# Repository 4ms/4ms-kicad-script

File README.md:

# 4ms Kicad Scripts
***All of these scripts are Works In Progress. Use at your own risk!!***

## Scripts

  * `makefp`: PCB plugins (python scripts) to create a Eurorack faceplate from a PCB. Automatically determines smallest standard size that will fit, creates an outline and rail mounting slots, replaces all panel components with holes (using a look-up table that you must edit if you're not using standard 4ms libraries), removes all SMT components and traces, and creates a copper GND plane on the back (connecting all holes to it). It's not perfect and often requires some manual clean-up.

  * `BOM-scripts`: EEschema plugins that produce a BOM properly formatted for a PCBA service.

  * `resistor_generator`: Generate a Kicad symbol library of standard resistor values (E96+E24) for a given SMT package and tolerance. Searches JLCPCB's database to populate a JLCPCB part number field, and also generates a valid Yageo part number.

  * `lib_scripts`: a series of scripts used to create a KiCad symbol library from a BOM CSV file and a group of schematics that share common parts. Originally written for the [OpenVentilator](https://gitlab.com/openventilator/openventilator) project. When importing projects into Kicad from other EDA software, a library is created for each imported project, so these scripts are handy for essentially merging all the individual project libraries into a single shared library (and throw in some useful information from a BOM file while it's at it). We also have used these scripts to create the latest 4ms symbol libraries (atomic part library) since we have all MPN etc information in the BOM files.

  * `lib_scripts/symLibConversion`: This script does some of the rote search-and-replacement when updating a legacy 4ms library schematic to the new atomic libraries.

  * `net_tools`: Some PCBnew python plugins for assigning nets to large amounts of items.

  * `grep-replace-globallabel-with-locallabel`: regex to replace all global labels with local labels in eechema. 

  * `XY-pos-file-convert`: A simple python script to convert Kicad's XY position file format to the one JLCPCB expects.

#### Deprecated Utilities ####

  * picknplace_assistant: Creates PDF files of front and back of PCB, showing the placement of each component. No longer being supported, as we've switched to using [Interactive HTML Bom](https://github.com/openscopeproject/InteractiveHtmlBom).

  * update\_kicad: OSX only. After you download and mount a Kicad nightly DMG, run this script to handle installing all the files, and properly merging the global fp/sym\_lib\_table files without having to manually add the 4ms libraries. This script also preserves your packages3d folder. No longer being supported, as our new library technique doesn't require modifying global library tables.

  * `gerbv shortcuts`. These are meant to be used with the old legacy gEDA gerbv program (not kicad's gerbv). They are templates that set the layer order and coloring to a standard format.

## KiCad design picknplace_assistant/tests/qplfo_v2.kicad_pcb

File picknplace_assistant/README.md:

Creates PDF files showing the placement of every component.

Forked from https://gist.github.com/pwuertz/152f15b2dadca9a74039aeab944714af

The pnpassist.py script can be run on the command line or in the PCB python terminal. The files in the plugin folders can be installed as plugins (see "How to install a plugin.md" file one directory up)

__Todo: Fork this in github/gist instead of just copying and modifying__

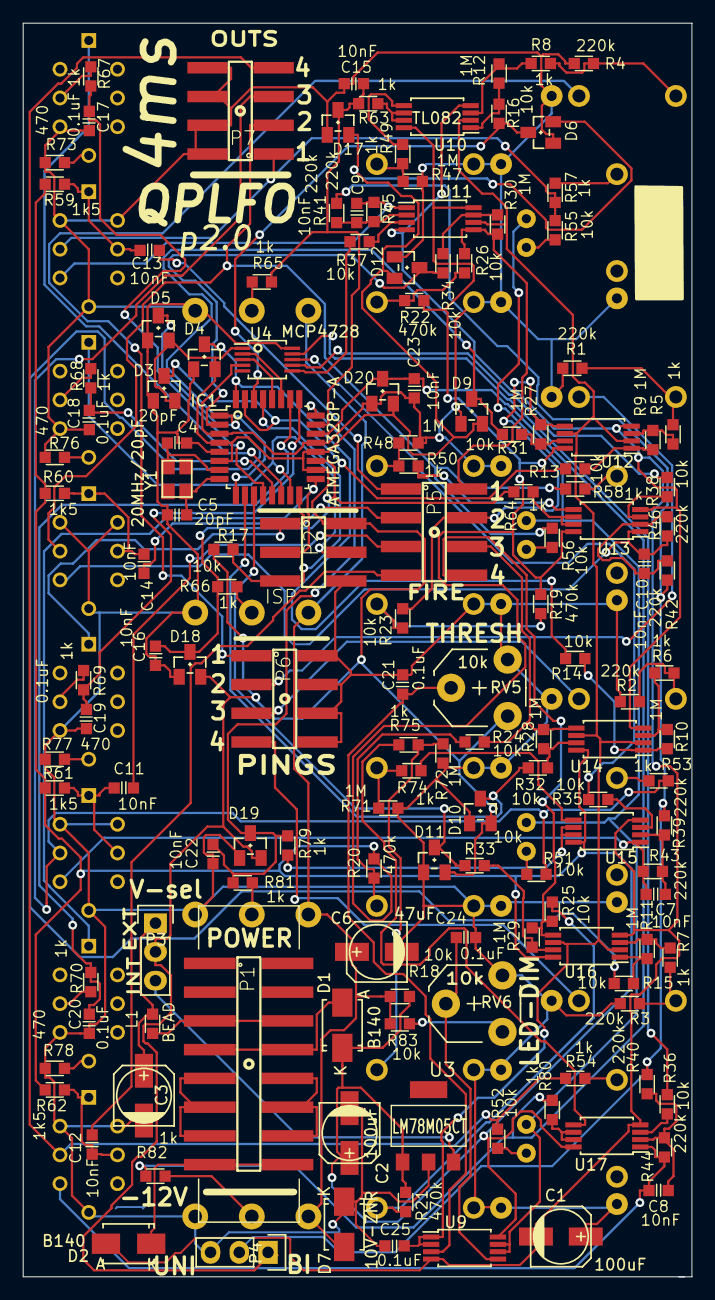
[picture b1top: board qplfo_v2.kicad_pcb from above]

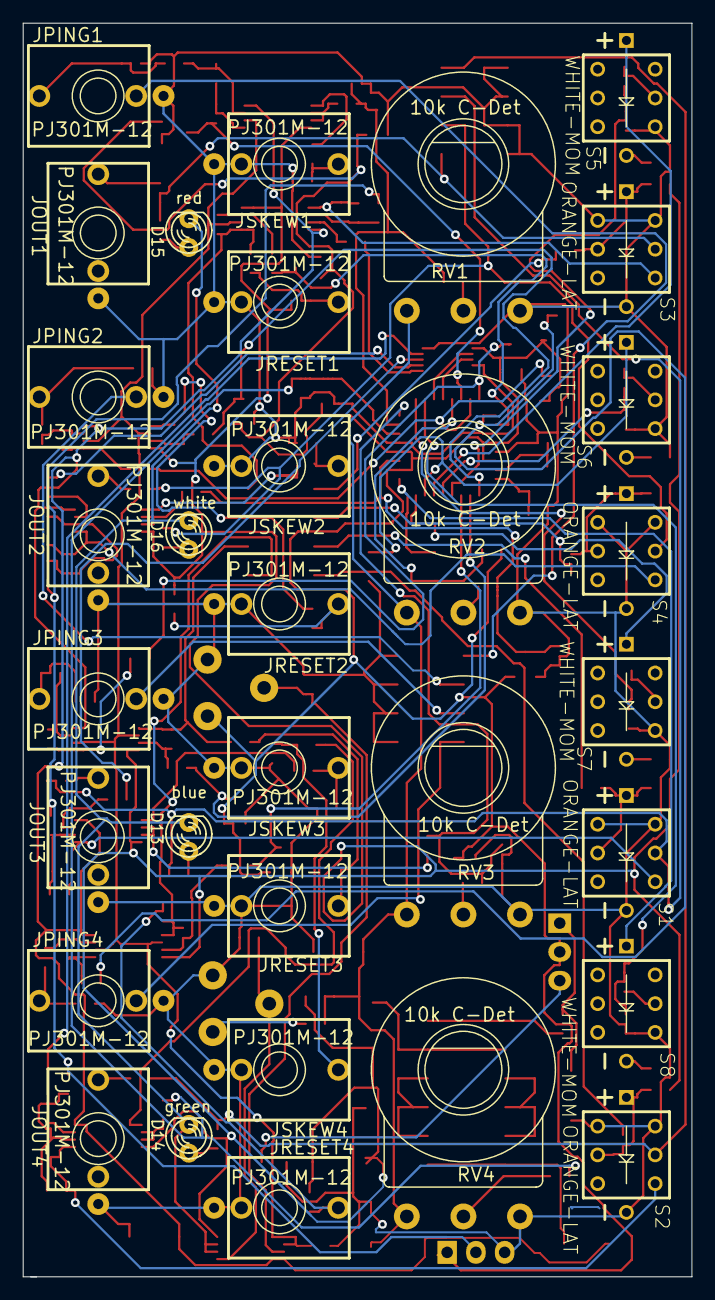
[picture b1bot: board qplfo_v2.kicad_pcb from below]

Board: 2 copper layers, 59.1 x 110.7 mm, 178 parts (32 on the bottom side), 131 nets.

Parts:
C1, C2, C3: 100uF; c_elec_5x5.3
C4, C5: 20pF; C0603
C6: 47uF; c_elec_5x5.3
C7, C8, C9, C10, C11, C12, C13, C14, C15, C16, C22, C23: 10nF; C0603
C17, C18, C19, C20, C21, C24, C25: 0.1uF; C0603
D1, D2: B140; Diode-SMA_Standard
D3, D4, D5, D6, D9, D10, D11, D12, D17, D18, D19, D20: BAT54S; SOT23
D7: 10V-ZNR; Diode-SMA_Standard
D13: blue; LED-3MM
D14: green; LED-3MM
D15: red; LED-3MM
D16: white; LED-3MM
IC1: ATMEGA328P-A; TQFP-32_7x7mm_Pitch0.8mm
JOUT1, JOUT2, JOUT3, JOUT4: PJ301M-12; PJ301M-12-FIX
JPING1, JPING2, JPING3, JPING4: PJ301M-12; PJ301M-12-FIX
JRESET1, JRESET2, JRESET3, JRESET4: PJ301M-12; PJ301M-12-FIX
JSKEW1, JSKEW2, JSKEW3, JSKEW4: PJ301M-12; PJ301M-12-FIX
L1: BEAD; R0603
P1: HE10-16; HEADER-2X8-SMT-SHROUDED
P2: ISP; HEADER-2X3-SMT
P3, P4: HEADER-MALE-1X3-TH; Pin_Header_Straight_1x03
P5: FIRE; HEADER-2X4-SMT
P6: PINGS; HEADER-2X4-SMT
P7: OUTS; HEADER-2X4-SMT
R1, R2, R3, R4, R39, R40, R41, R42, R43, R44, R45, R46: 220k; R0603
R5, R6, R7, R8, R49, R50, R53, R54, R57, R58, R63, R64, R65, R66, R67, R68, R69, R70, R74, R75, R79, R80, R81, R82: 1k; R0603
R9, R10, R11, R12, R27, R28, R29, R30, R47, R48, R71, R72: 1M; R0603
R13, R14, R15, R16, R17, R18, R23, R24, R25, R26, R31, R32, R33, R34, R35, R36, R37, R38, R51, R52, R55, R56, R83: 10k; R0603
R19, R20, R21, R22: 470k; R0603
R59, R60, R61, R62: 1k5; R0603
R73, R76, R77, R78: 470; R0603
RV1, RV2, RV3, RV4: 10k C-Det; 16MM-RV16AF-4A
RV5, RV6: 10k; Potentiometer_VishaySpectrol-Econtrim-Type36M
S1, S2, S3, S4: ORANGE-LAT; BUTTON-LED-PB61303
S5, S6, S7, S8: WHITE-MOM; BUTTON-LED-PB61303
U3: LM78M05CT; SOT223
U4: MCP4728; MSOP-10_3x3mm_Pitch0.5mm
U9, U10, U11, U12, U13, U14, U15, U16, U17: TL082; TSSOP-8_4.4x3mm_Pitch0.65mm
Y1: 20MHz/20pF; crystal_FA238-TSX3225

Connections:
+5V: D3.2, D4.2, D5.2, D6.2, D9.2, D10.2, D11.2, D12.2, D17.2, D18.2, D19.2, D20.2, IC1.4, IC1.6, IC1.18, IC1.20, P2.2, P3.2, P4.1, R17.1, RV5.1, U4.1
+12V: C2.1, D1.1, R18.2, R19.2, R20.2, R21.2, R22.2, R59.1, R60.1, R61.1, R62.1, U3.1, U9.8, U10.8, U11.8, U12.8, U13.8, U14.8, U15.8, U16.8, U17.8
-12V: C1.2, D2.2, U9.4, U10.4, U11.4, U12.4, U13.4, U14.4, U15.4, U16.4, U17.4
ENVRAW1: R37.2, U4.6
ENVRAW2: R38.2, U4.7
ENVRAW3: R35.2, U4.8
ENVRAW4: R36.2, U4.9
GND: C1.1, C2.2, C3.2, C4.2, C5.2, C6.2, C15.2, C16.2, C17.1, C18.1, C19.1, C20.1, C21.2, C22.2, C23.2, C24.2, C25.2, D3.1, D4.1, D5.1, D6.1, D7.1, D9.1, D10.1, D11.1, D12.1, D17.1, D18.1, D19.1, D20.1, IC1.3, IC1.5, IC1.21, JOUT1.2, JOUT2.2, JOUT3.2, JOUT4.2, JPING1.2, JPING2.2, JPING3.2, JPING4.2, JRESET1.2, JRESET1.3, JRESET2.2, JRESET2.3, JRESET3.2, JRESET3.3, JRESET4.2, JRESET4.3, JSKEW1.2, JSKEW1.3, JSKEW2.2, JSKEW2.3, JSKEW3.2, JSKEW3.3, JSKEW4.2, JSKEW4.3, P2.6, P4.3, P6.2, P6.4, P6.6, P6.8, P7.2, P7.4, P7.6, P7.8, R1.2, R2.2, R3.2, R4.2, R47.1, R48.1, R71.1, R72.1, R73.1, R76.1, R77.1, R78.1, RV1.3, RV2.3, RV3.3, RV4.3, RV5.3, RV6.3, S1.1, S1.4, S1.8, S2.1, S2.4, S2.8, S3.1, S3.4, S3.8, S4.1, S4.4, S4.8, S5.6, S6.6, S7.6, S8.6, U3.2, U4.4, U4.10
unnamed: C3.1, L1.2, P3.1
unnamed: C4.1, IC1.7, Y1.2
unnamed: C5.1, IC1.8, Y1.1
unnamed: C7.1, R43.1, S1.6, U15.1
unnamed: C7.2, R39.1, R43.2, U15.2
unnamed: C8.1, R44.1, S2.6, U17.1
unnamed: C8.2, R40.1, R44.2, U17.2
unnamed: C9.1, R45.1, S3.6, U11.1
unnamed: C9.2, R41.1, R45.2, U11.2
unnamed: C10.1, R46.1, S4.6, U13.1
unnamed: C10.2, R42.1, R46.2, U13.2
unnamed: C11.1, R61.2, S1.2, S1.7
unnamed: C12.1, R62.2, S2.2, S2.7
unnamed: C13.1, R59.2, S3.2, S3.7
unnamed: C14.1, R60.2, S4.2, S4.7
unnamed: C21.1, RV5.2, U9.3
unnamed: C24.1, RV6.2, U9.5
unnamed: D1.2, P1.7, P1.8
unnamed: D2.1, P1.15, P1.16
unnamed: D13.1, R51.1
unnamed: D14.1, R52.1
unnamed: D15.1, R55.1
unnamed: D16.1, R56.1
unnamed: IC1.27, U4.2
unnamed: IC1.28, U4.3
unnamed: IC1.29, P2.5, R17.2
unnamed: JOUT1.1, R57.1
unnamed: JOUT2.1, R58.1
unnamed: JOUT3.1, R53.1
unnamed: JOUT4.1, R54.1
unnamed: JPING1.1, R4.1, R8.2
unnamed: JPING2.1, R1.1, R5.2
unnamed: JPING3.1, R2.1, R6.2
unnamed: JPING4.1, R3.1, R7.2
unnamed: JRESET1.1, R22.1, R26.2
unnamed: JRESET2.1, R19.1, R23.2
unnamed: JRESET3.1, R20.1, R24.2
unnamed: JRESET4.1, R21.1, R25.2
unnamed: JSKEW1.1, R47.2, R49.2
unnamed: JSKEW2.1, R48.2, R50.2
unnamed: JSKEW3.1, R71.2, R74.2
unnamed: JSKEW4.1, R72.2, R75.2
unnamed: L1.1, P1.5, P1.6
unnamed: P1.10, P1.12, P1.14
unnamed: P1.9, P1.11, P1.13
unnamed: P3.3, U3.3
unnamed: R5.1, R9.2, U12.3
unnamed: R10.1, R14.1, U14.1
unnamed: R6.1, R10.2, U14.3
unnamed: R11.1, R15.1, U16.1
unnamed: R7.1, R11.2, U16.3
unnamed: R12.1, R16.1, U10.1
unnamed: R8.1, R12.2, U10.3
unnamed: R9.1, R13.1, U12.1
unnamed: R27.1, R31.1, U12.7
unnamed: R28.1, R32.1, U14.7
unnamed: R29.1, R33.1, U16.7
unnamed: R30.1, R34.1, U11.7
unnamed: R35.1, U15.3
unnamed: R36.1, U17.3
unnamed: R37.1, U11.3
unnamed: R38.1, U13.3
unnamed: R49.1, U10.5
unnamed: R50.1, U13.5
unnamed: R63.2, U10.6, U10.7
unnamed: R64.2, U13.6, U13.7
unnamed: R65.2, RV1.2
unnamed: R66.2, RV2.2
unnamed: R67.2, S5.5
unnamed: R68.2, S6.5
unnamed: R69.2, S7.5
unnamed: R70.2, S8.5
unnamed: R73.2, S5.8
unnamed: R74.1, U15.5
unnamed: R75.1, U17.5
unnamed: R76.2, S6.8
unnamed: R77.2, S7.8
unnamed: R78.2, S8.8
unnamed: R79.2, U15.6, U15.7
unnamed: R80.2, U17.6, U17.7
unnamed: R81.2, RV3.2
unnamed: R82.2, RV4.2
unnamed: R83.1, RV6.1
OUT1J: P7.1, R55.2, R57.2, S3.5
OUT2J: P7.3, R56.2, R58.2, S4.5
OUT3J: P7.5, R51.2, R53.2, S1.5
OUT4J: P7.7, R52.2, R54.2, S2.5
PING1: D6.3, IC1.30, R16.2
PING1SW: JPING1.3, P6.1
PING2: D3.3, IC1.31, R13.2
PING2SW: JPING2.3, P6.3
PING3: D4.3, IC1.32, R14.2
PING3SW: JPING3.3, P6.5
PING4: D5.3, IC1.1, R15.2
PING4SW: JPING4.3, P6.7
RESET1: D12.3, IC1.2, R34.2
RESET2: D9.3, IC1.9, R31.2
RESET3: D10.3, IC1.10, R32.2
RESET4: D11.3, IC1.11, R33.2
RESETMUTE1: C13.2, P5.1
RESETMUTE1B: P5.2, R26.1, R30.2, U11.5
RESETMUTE2: C14.2, P5.3
RESETMUTE2B: P5.4, R23.1, R27.2, U12.5
RESETMUTE3: C11.2, P5.5
RESETMUTE3B: P5.6, R24.1, R28.2, U14.5
RESETMUTE4: C12.2, P5.7
RESETMUTE4B: P5.8, R25.1, R29.2, U16.5
SKEW1-ADC: C15.1, D17.3, IC1.23, R63.1, R65.1
SKEW2-ADC: C22.1, D19.3, IC1.24, R79.1, R81.1
SKEW3-ADC: C16.1, D18.3, IC1.19, R64.1, R66.1
SKEW4-ADC: C23.1, D20.3, IC1.22, R80.1, R82.1
TAP1: C17.2, IC1.12, R67.1
TAP2: C18.2, IC1.13, R68.1
TAP3: C19.2, IC1.25, R69.1
TAP4: C20.2, IC1.26, R70.1
TAPLED1: IC1.14, S5.7
TAPLED2: IC1.15, P2.4, S6.7
TAPLED3: IC1.16, P2.1, S7.7
TAPLED4: IC1.17, P2.3, S8.7
VAA: C6.1, D7.2, R18.1, R83.2, RV1.1, RV2.1, RV3.1, RV4.1
VLED: D13.2, D14.2, D15.2, D16.2, U9.6, U9.7
Vpolar: P4.2, R39.2, R40.2, R41.2, R42.2
Vthresh: C25.1, U9.1, U9.2, U10.2, U11.6, U12.2, U12.6, U14.2, U14.6, U16.2, U16.6
